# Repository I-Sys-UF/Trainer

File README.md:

# I.Sys Programming Trainer の使い方

## KiCAD プロジェクト

`./ISysProgrammingTrainerTypeA/` 以下に配置

### 回路図

<div align="center">
  
</div>

### 基板デザイン

<div align="center">
  
</div>

### 3D プレビュー

<div align="center">

</div>

## 進め方

<https://i-sys-uf.github.io/docs/edu/getting_started_programming> を読みながら進めてください

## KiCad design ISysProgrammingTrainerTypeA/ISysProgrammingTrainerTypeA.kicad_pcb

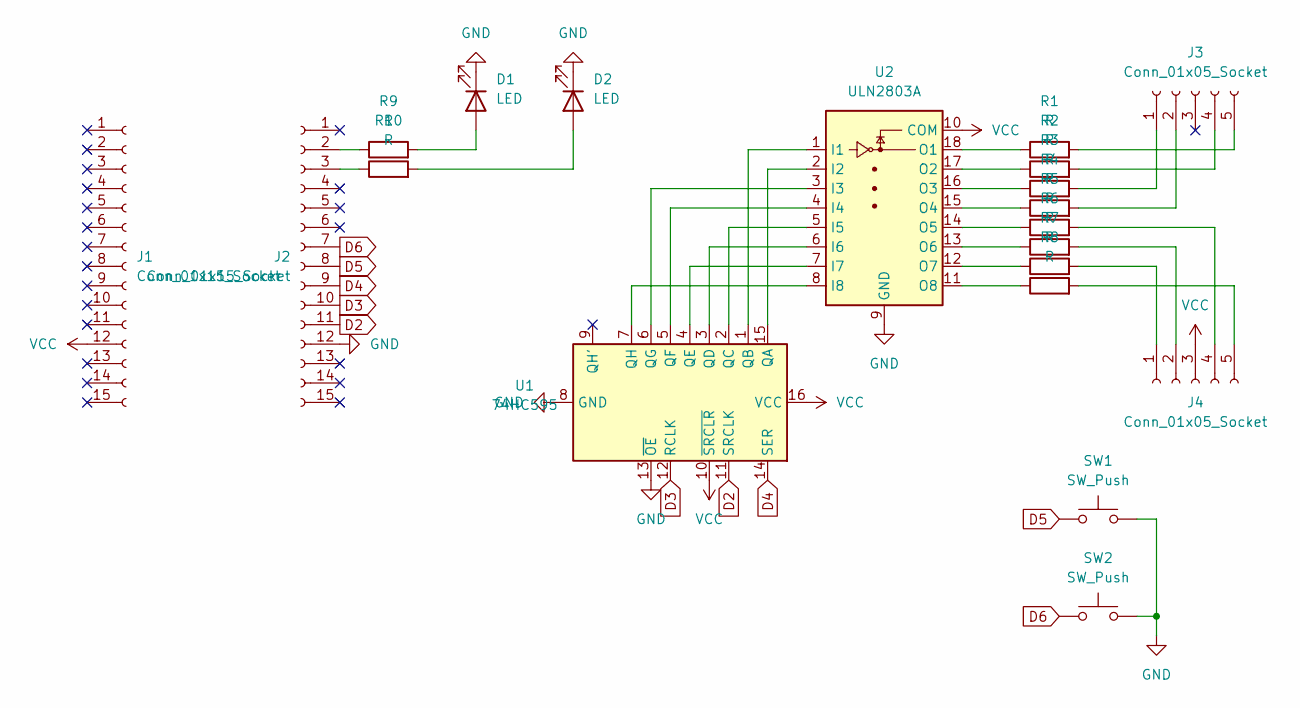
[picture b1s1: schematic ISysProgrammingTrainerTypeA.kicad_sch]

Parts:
D1, D2: LED; LED_D5.0mm
J1, J2: Conn_01x15_Socket; PinSocket_1x15_P2.54mm_Vertical
J3, J4: Conn_01x05_Socket; PinSocket_1x05_P2.54mm_Vertical
R1, R2, R3, R4, R5, R6, R7, R8, R9, R10: R; R_Axial_DIN0207_L6.3mm_D2.5mm_P10.16mm_Horizontal
SW1, SW2: SW_Push; SW_PUSH_6mm
U1: 74HC595; DIP-16_W7.62mm_Socket
U2: ULN2803A; DIP-18_W7.62mm_Socket

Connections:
D2: J2.11, U1.11 (SRCLK)
D3: J2.10, U1.12 (RCLK)
D4: J2.9, U1.14 (SER)
D5: J2.8, SW1.1
D6: J2.7, SW2.1
GND: D1.1 (K), D2.1 (K), J2.12, SW1.2, SW2.2, U1.8 (GND), U1.13 (~OE), U2.9 (GND)
unnamed: D1.2 (A), R9.2
unnamed: D2.2 (A), R10.2
unnamed: J2.2, R9.1
unnamed: J2.3, R10.1
unnamed: J3.1, R3.2
unnamed: J3.2, R4.2
unnamed: J3.4, R2.2
unnamed: J3.5, R1.2
unnamed: J4.1, R7.2
unnamed: J4.2, R6.2
unnamed: J4.4, R5.2
unnamed: J4.5, R8.2
unnamed: U1.15 (QA), U2.2 (I2)
unnamed: U1.1 (QB), U2.1 (I1)
unnamed: U1.2 (QC), U2.5 (I5)
unnamed: U1.3 (QD), U2.6 (I6)
unnamed: U1.4 (QE), U2.7 (I7)
unnamed: U1.5 (QF), U2.4 (I4)
unnamed: U1.6 (QG), U2.3 (I3)
unnamed: U1.7 (QH), U2.8 (I8)
unnamed: R1.1, U2.18 (O1)
unnamed: R2.1, U2.17 (O2)
unnamed: R3.1, U2.16 (O3)
unnamed: R4.1, U2.15 (O4)
unnamed: R5.1, U2.14 (O5)
unnamed: R6.1, U2.13 (O6)
unnamed: R7.1, U2.12 (O7)
unnamed: R8.1, U2.11 (O8)
VCC: J1.12, J4.3, U1.10 (~SRCLR), U1.16 (VCC), U2.10 (COM)

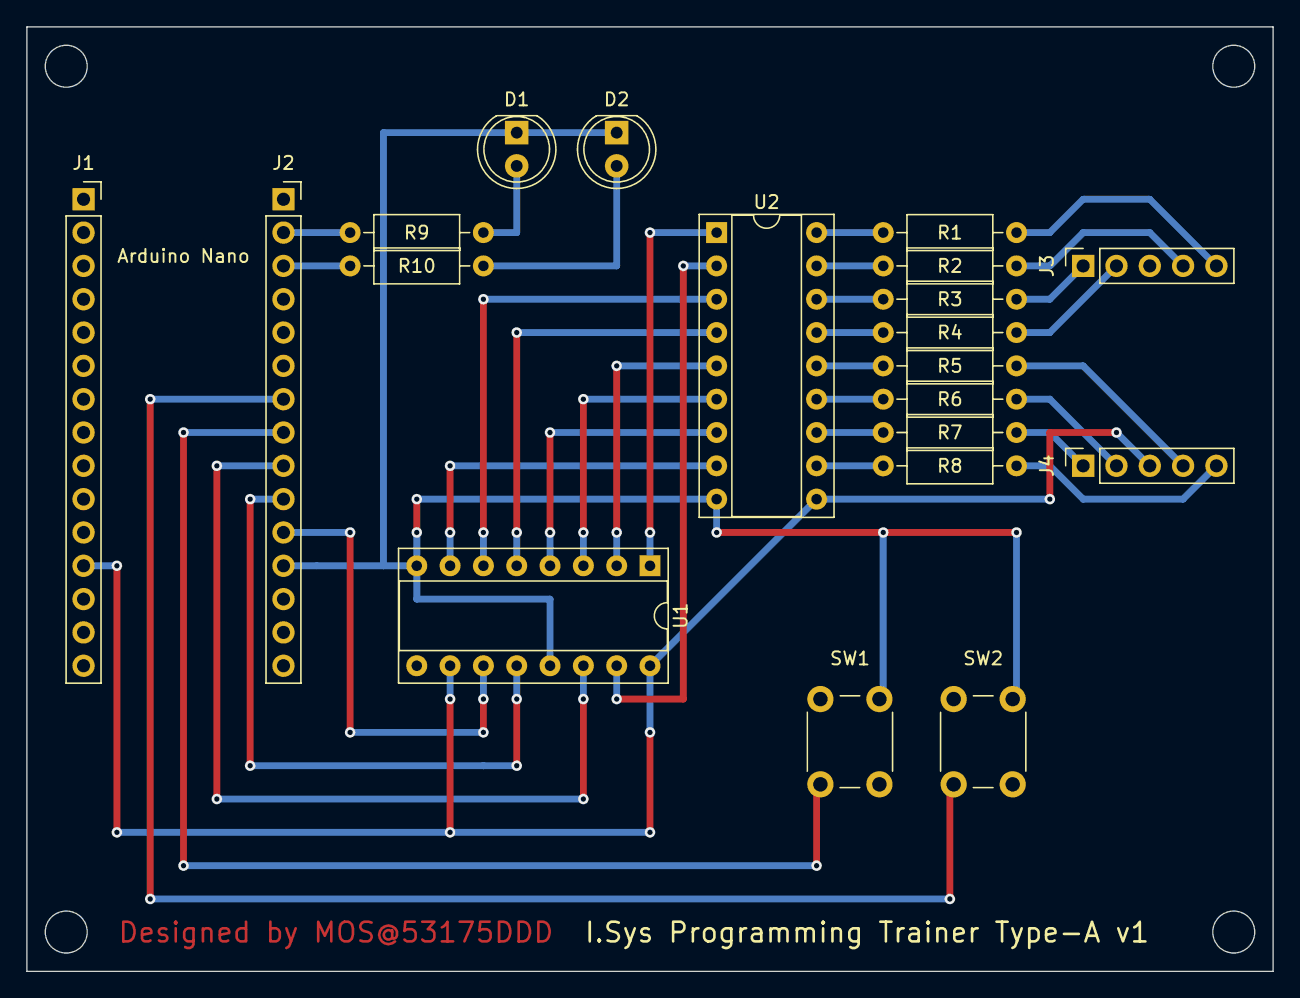
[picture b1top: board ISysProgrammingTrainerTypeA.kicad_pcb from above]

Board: 2 copper layers, 95.0 x 72.0 mm, 20 parts (0 on the bottom side), 35 nets.

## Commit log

2023-12-07 rename and replace
2023-12-07 タイマー割り込みを使うように変更
2023-12-07 define 文を追加
2023-12-07 目次作成
2023-12-07 目次追加
2023-12-07 基板データ作成
2023-12-07 シルク印刷にリポジトリのリンクを追加
2023-12-07 Train を追加
2023-12-08 fix o -> 0
2023-12-08 LED_VRAM に突っ込む値を変更
2023-12-08 トレーニングプログラムを追加
2023-12-08 押された瞬間にだけ LED が光るように変更
2023-12-09 bug fix
    - LED_OUT が存在しない問題を修正
    - `sprintf` が float を表示できない問題を修正
2023-12-13 回路図の配置を変更
2023-12-13 README 更新．画像を追加
2024-05-01 ドキュメント追加
2024-05-01 誤字修正
2024-05-07 Update issue templates
2024-05-09 Rename TrainingKit-demo.ino to demo.ino
2024-05-09 fix link
2024-11-08 シルク印刷を追加
    `Arduino Nano` の刻印を追加
